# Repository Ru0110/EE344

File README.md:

# EE344
Auto-dialling Alarm System for Temperature and Humidity Monitoring

## File organization
The following folders will be present in the root directory of the project:
- `energy_meter`: Contains KiCad design files for the sensing unit PCB
- `Software`: Contains all firmware used in the project
    - `RP2040_code`: Source code for the firmware of the sensing unit written using the RP2040 C/C++ SDK. The code may be built using CMake or the uf2 file in the build subdirectory may be flashed directly to the RPi Pico W.
    - `arduino_code`: Source code for the sensing unit based on arduino. Based on code provided by Analog Devices for the EVAL-ACE9000 SHIELDZ board.
    - `central_code`: Source code for the central unit written in MicroPython
    - Other python files are for setting up a TCP client to test data logging
- `CAD`: Contains files for the enclosures of the sensing unit and central unit  
- `Test`: Contains test data from a long-term test using an Air Conditioner
- `central_unit`: Contains KiCad design files for a central unit with a SIM800L module. This is not used in the final prototype but may be useful for future iterations
- `Website`: Contains Code for a locally hosted website to view real-time data from the sensing units 
- Documentation file
- README file (this file)

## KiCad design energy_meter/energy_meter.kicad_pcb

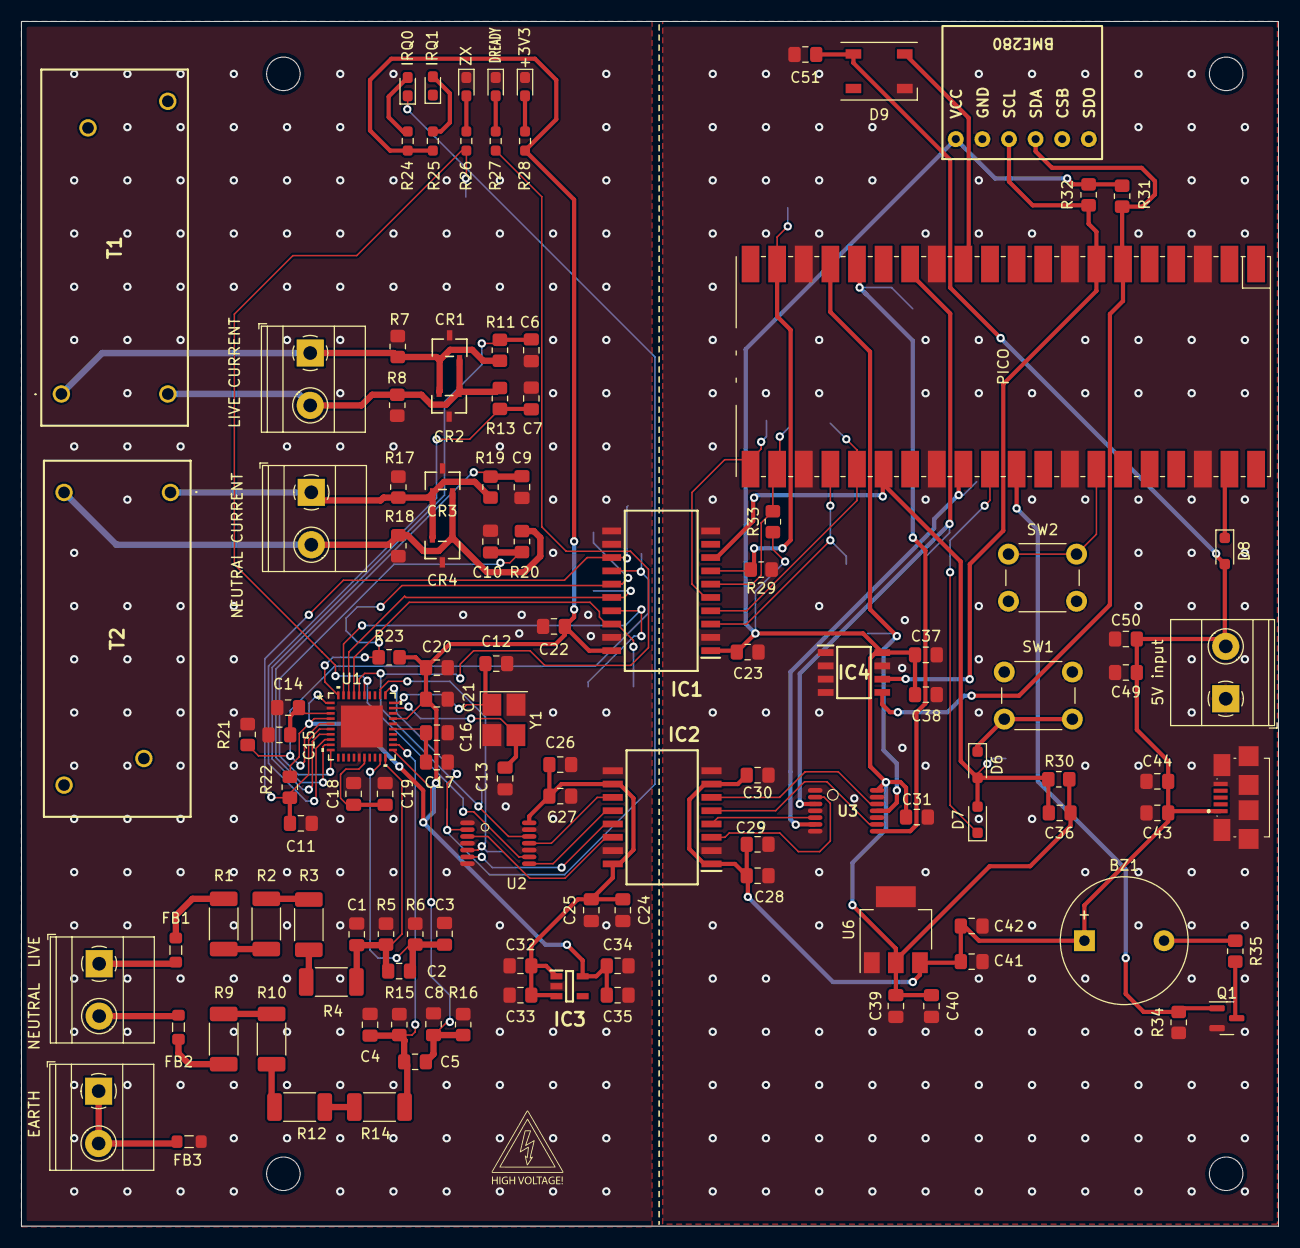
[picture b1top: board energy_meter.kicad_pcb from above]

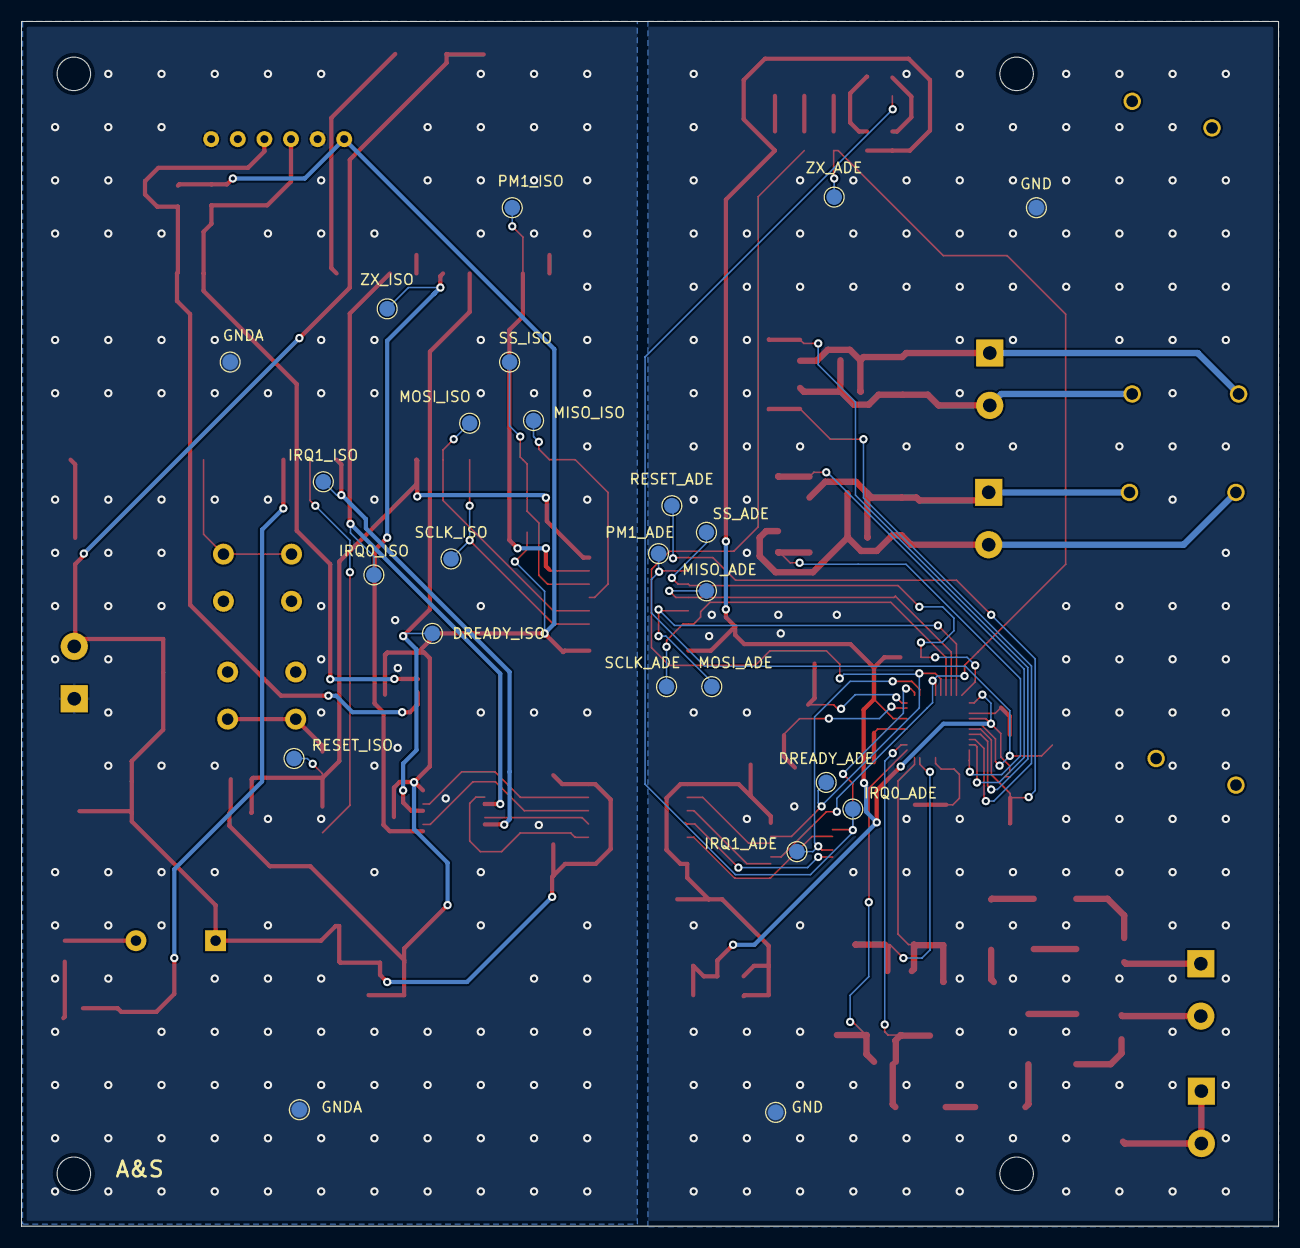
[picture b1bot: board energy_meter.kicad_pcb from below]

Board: 2 copper layers, 120.0 x 115.0 mm, 149 parts (24 on the bottom side), 77 nets.

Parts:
5V input: 5V_SMPS; TerminalBlock_Phoenix_MKDS-1,5-2_1x02_P5.00mm_Horizontal
+3V3: LED; LED_0603_1608Metric_Pad1.05x0.95mm_HandSolder
BZ1: Buzzer; Buzzer_12x9.5RM7.6
C1, C3, C4, C6, C7, C8, C9, C10: 0.022u; C_0805_2012Metric_Pad1.18x1.45mm_HandSolder
C2, C5: 51p; C_0805_2012Metric_Pad1.18x1.45mm_HandSolder
C11, C36: 1u; C_0805_2012Metric_Pad1.18x1.45mm_HandSolder
C12, C13: 18p; C_0805_2012Metric_Pad1.18x1.45mm_HandSolder
C14, C16, C18, C20, C22, C23, C24, C26, C28, C30, C31, C33, C35, C38, C39, C41, C44, C49, C51: 0.1u; C_0805_2012Metric_Pad1.18x1.45mm_HandSolder
C15, C17, C19, C37: 4.7u; C_0805_2012Metric_Pad1.18x1.45mm_HandSolder
C21, C25, C27, C29, C32, C34, C40, C42: 10u; C_0805_2012Metric_Pad1.18x1.45mm_HandSolder
C43, C50: 22u; C_0805_2012Metric_Pad1.18x1.45mm_HandSolder
CR1, CR2, CR3, CR4: MMBD4148SE; SOT-23TO-236_318-AT_OSI
D6, D7, D8: D_Schottky; D_SOD-323_HandSoldering
D9: WS2812B; LED_WS2812B_PLCC4_5.0x5.0mm_P3.2mm
DREADY: LED; LED_0603_1608Metric_Pad1.05x0.95mm_HandSolder
DREADY_ADE: TestPoint; TestPoint_Pad_D1.5mm
DREADY_ISO: TestPoint; TestPoint_Pad_D1.5mm
FB1, FB2, FB3: FerriteBead; L_0805_2012Metric_Pad1.05x1.20mm_HandSolder
GND: TestPoint; TestPoint_Pad_D1.5mm
GND#2: TestPoint; TestPoint_Pad_D1.5mm
GNDA: TestPoint; TestPoint_Pad_D1.5mm
GNDA#2: TestPoint; TestPoint_Pad_D1.5mm
H1, H2, H3, H4: MountingHole; MountingHole_3.2mm_M3
IC1: ADUM4151BRIZ; SOIC127P1031X264-20N
IC2: ADUM6404ARIZ; SOIC127P1032X265-16N
IC3: ADP122AUJZ-3.3-R7; SOT95P280X100-5N
IC4: 24LC32A_SN; SOIC127P600X175-8N
IRQ0, IRQ1: LED; LED_0603_1608Metric_Pad1.05x0.95mm_HandSolder
IRQ0_ADE, IRQ0_ISO, IRQ1_ADE, IRQ1_ISO: TestPoint; TestPoint_Pad_D1.5mm
J1, J2: Screw_Terminal_01x02; TerminalBlock_Phoenix_MKDS-1,5-2_1x02_P5.00mm_Horizontal
J3: MicroUSB; ZX62AB5PA31
LIVE CURRENT: IA_in; TerminalBlock_Phoenix_MKDS-1,5-2_1x02_P5.00mm_Horizontal
MISO_ADE: TestPoint; TestPoint_Pad_D1.5mm
MISO_ISO: TestPoint; TestPoint_Pad_D1.5mm
MOSI_ADE: TestPoint; TestPoint_Pad_D1.5mm
MOSI_ISO: TestPoint; TestPoint_Pad_D1.5mm
NEUTRAL CURRENT: IB_in; TerminalBlock_Phoenix_MKDS-1,5-2_1x02_P5.00mm_Horizontal
PICO: Pico_SMD_NODEBUG; RPi_PicoW_SMD
PM1_ADE, PM1_ISO: TestPoint; TestPoint_Pad_D1.5mm
Q1: Q_NMOS_SGD; SOT-23
R1, R2, R3, R4, R9, R10, R12, R14: 200k; R_2010_5025Metric_Pad1.40x2.65mm_HandSolder
R5, R6, R11, R13, R15, R16, R19, R20, R35: 1k; R_0805_2012Metric_Pad1.20x1.40mm_HandSolder
R7, R8, R17, R18: 40.2; R_0805_2012Metric_Pad1.20x1.40mm_HandSolder
R21: 10K; R_0805_2012Metric_Pad1.20x1.40mm_HandSolder
R22, R23, R29, R30, R31, R32, R33, R34: 10k; R_0805_2012Metric_Pad1.20x1.40mm_HandSolder
R24, R25, R26: 3K; R_0603_1608Metric_Pad0.98x0.95mm_HandSolder
R27, R28: 3k; R_0603_1608Metric_Pad0.98x0.95mm_HandSolder
RESET_ADE: TestPoint; TestPoint_Pad_D1.5mm
RESET_ISO: TestPoint; TestPoint_Pad_D1.5mm
SCLK_ADE: TestPoint; TestPoint_Pad_D1.5mm
SCLK_ISO: TestPoint; TestPoint_Pad_D1.5mm
SS_ADE: TestPoint; TestPoint_Pad_D1.5mm
SS_ISO: TestPoint; TestPoint_Pad_D1.5mm
SW1, SW2: SW_Push; SW_PUSH_6mm
T1: IA_in; T60404E4626X502
T2: IB_in; T60404E4626X502
U1: ADE9000ACPZ; ADE9000ACPZ_ADI
U2, U3: SN74LV4T125PWR; PW0014A_N
U5: BME280; BME_breakout
U6: AMS1117-3.3; SOT-223-3_TabPin2
Y1: Crystal_GND24; Crystal_SMD_3225-4Pin_3.2x2.5mm_HandSoldering
ZX: LED; LED_0603_1608Metric_Pad1.05x0.95mm_HandSolder
ZX_ADE: TestPoint; TestPoint_Pad_D1.5mm
ZX_ISO: TestPoint; TestPoint_Pad_D1.5mm

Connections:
+3V3_ADE: C20.1, C21.1, C22.1, C34.1, C35.1, IC1.20 (VDD2), IC3.5 (VOUT), R22.1, R23.2, R24.1, R25.1, R28.1, U1.1 (PULL_HIGH), U1.4 (PM0), U1.27 (VDD)
+3V3_ISO: C23.2, C31.1, C36.1, C37.1, C38.1, C39.1, C40.1, IC1.1 (VDD1), IC4.8 (VCC), R30.1, R31.1, R32.1, R33.1, U3.14 (VCC), U5.1 (VCC), U6.2 (VO)
+5V_ADE: C24.1, C25.1, C26.1, C27.1, C32.1, C33.1, IC2.10 (VSEL), IC2.16 (VISO), IC3.1 (VIN), IC3.3 (EN), U2.14 (VCC)
+5V_PICO: 5V input.2, BZ1.1 (+), C28.1, C29.1, C30.2, C41.1, C42.1, C43.1, C44.1, C49.1, C50.1, C51.1, D8.2 (A), D9.1 (VDD), IC2.1 (VDD1), IC2.7 (VDDL), J3.1, U6.3 (VI)
AVDDOUT: C16.1, C17.1, U1.25 (AVDDOUT)
BUZZER: PICO.31 (GPIO26_ADC0), Q1.1 (G), R34.1
DREADY_ADE: DREADY_ADE.1, R27.1, U1.36 (CF4/*EVENT/DREADY), U2.12 (4A)
DREADY_ISO: DREADY_ISO.1, PICO.17 (GPIO13), U3.11 (4Y)
DVDDOUT: C14.1, C15.1, U1.3 (DVDDOUT)
EARTH: FB3.2, J2.1, J2.2
GND: +3V3.1 (K), C1.2, C3.2, C4.2, C6.2, C7.1, C8.2, C9.2, C10.1, C11.2, C12.2, C13.2, C14.2, C15.2, C16.2, C17.2, C18.2, C19.2, C20.2, C21.2, C22.2, C24.2, C25.2, C26.2, C27.2, C32.2, C33.2, C34.2, C35.2, CR1.3, CR2.3, CR3.3, CR4.3, DREADY.1 (K), FB3.1, GND.1, GND#2.1, IC1.11 (GND2_1), IC1.12 (VIC), IC1.19 (GND2_2), IC2.9 (GNDISO_1), IC2.15 (GNDISO_2), IC3.2 (GND), R5.1, R6.1, R7.2, R8.1, R15.1, R16.1, R17.2, R18.1, R21.2, U1.2 (DGND), U1.15 (REFGND), U1.26 (AGND), U1.28 (GND), U1.41 (EPAD), U2.1 (1OE_N), U2.4 (2OE_N), U2.7 (GND), U2.10 (3OE_N), U2.13 (4OE_N), Y1.2, Y1.4, ZX.1 (K)
GNDA: 5V input.1, C23.1, C28.2, C29.2, C30.1, C31.2, C37.2, C38.2, C39.2, C40.2, C41.2, C42.2, C43.2, C44.2, C49.2, C50.2, C51.2, D9.3 (VSS), GNDA.1, GNDA#2.1, IC1.2 (GND1_1), IC1.10 (GND1_2), IC2.2 (GND1_1), IC2.8 (GND1_2), IC4.1 (A0), IC4.2 (A1), IC4.3 (A2), IC4.4 (VSS), IC4.7 (WP), J3.5, J3.MP1, J3.MP2, J3.MP3, J3.MP4, J3.MP5, J3.MP6, PICO.3 (GND), PICO.8 (GND), PICO.13 (GND), PICO.18 (GND), PICO.23 (GND), PICO.28 (GND), PICO.33 (AGND), PICO.38 (GND), Q1.2 (S), R29.1, R34.2, SW1.1, SW2.2, U3.1 (1OE_N), U3.4 (2OE_N), U3.7 (GND), U3.10 (3OE_N), U3.13 (4OE_N), U5.2 (GND), U5.6 (SDO), U6.1 (GND)
IAN: C7.2, R13.2, U1.8 (IAN)
IAP: C6.1, R11.2, U1.7 (IAP)
IBN: C10.2, R20.2, U1.10 (IBN)
IBP: C9.1, R19.2, U1.9 (IBP)
IRQ0_ADE: IRQ0.1 (K), IRQ0_ADE.1, U1.31 (*IRQ0), U2.2 (1A)
IRQ0_ISO: IRQ0_ISO.1, PICO.14 (GPIO10), U3.3 (1Y)
IRQ1_ADE: IRQ1_ADE.1, U1.32 (*IRQ1), U2.5 (2A)
IRQ1_ISO: IRQ1_ISO.1, PICO.29 (GPIO22), U3.6 (2Y)
MISO_ADE: IC1.16 (SO), MISO_ADE.1, U1.38 (MISO)
MISO_ISO: IC1.5 (MI), MISO_ISO.1, PICO.21 (GPIO16)
MOSI_ADE: IC1.17 (SI), MOSI_ADE.1, U1.39 (MOSI)
MOSI_ISO: IC1.4 (MO), MOSI_ISO.1, PICO.25 (GPIO19)
unnamed: BZ1.2 (-), R35.1
unnamed: IRQ0.2 (A), R24.2
unnamed: IRQ1.2 (A), R25.2
unnamed: R26.2, ZX.2 (A)
unnamed: DREADY.2 (A), R27.2
unnamed: +3V3.2 (A), R28.2
unnamed: D6.1 (K), SW1.2
unnamed: D8.1 (K), PICO.39 (VSYS)
unnamed: FB1.1, R1.1
unnamed: FB2.1, R9.1
unnamed: IC2.14 (VIA), U2.3 (1Y)
unnamed: IC2.13 (VIB), U2.6 (2Y)
unnamed: IC2.12 (VIC), U2.8 (3Y)
unnamed: IC2.11 (VID), U2.11 (4Y)
unnamed: IC2.3 (VOA), U3.2 (1A)
unnamed: IC2.4 (VOB), U3.5 (2A)
unnamed: IC2.5 (VOC), U3.9 (3A)
unnamed: IC2.6 (VOD), U3.12 (4A)
unnamed: CR1.1, CR2.2, LIVE CURRENT.1, R7.1, R11.1, T1.1
unnamed: CR1.2, CR2.1, LIVE CURRENT.2, R8.2, R13.1, T1.4
unnamed: CR3.1, CR4.2, NEUTRAL CURRENT.1, R17.1, R19.1, T2.1
unnamed: CR3.2, CR4.1, NEUTRAL CURRENT.2, R18.2, R20.1, T2.4
unnamed: Q1.3 (D), R35.2
unnamed: R1.2, R2.1
unnamed: R2.2, R3.1
unnamed: R3.2, R4.1
unnamed: R9.2, R10.1
unnamed: R10.2, R12.1
unnamed: R12.2, R14.1
unnamed: C13.1, U1.29 (CLKIN), Y1.3
unnamed: C12.1, U1.30 (CLKOUT), Y1.1
unnamed: PICO.34 (GPIO28_ADC2), SW2.1
PM1_ADE: IC1.14 (VOA), PM1_ADE.1, R21.1, U1.5 (PM1)
PM1_ISO: IC1.7 (VIA), PICO.19 (GPIO14), PM1_ISO.1, R29.2
REF: C18.1, C19.1, U1.16 (REF)
RESET_ADE: C11.1, IC1.13 (VOB), R22.2, RESET_ADE.1, U1.6 (*RESET)
RESET_ISO: C36.2, D6.2 (A), D7.2 (A), IC1.8 (VIB), PICO.26 (GPIO20), R30.2, RESET_ISO.1
RESET_PICO: D7.1 (K), PICO.30 (RUN)
SCLK_ADE: IC1.18 (SCLK), SCLK_ADE.1, U1.37 (SCLK)
SCLK_ISO: IC1.3 (MCLK), PICO.24 (GPIO18), SCLK_ISO.1
SCL_PICO: IC4.6 (SCL), PICO.7 (GPIO5), R32.2, U5.3 (SCL)
SDA_PICO: IC4.5 (SDA), PICO.6 (GPIO4), R31.2, U5.4 (SDA)
SS_ADE: IC1.15 (~SSS), R23.1, SS_ADE.1, U1.40 (*SS)
SS_ISO: IC1.6 (~MSS), PICO.22 (GPIO17), R33.2, SS_ISO.1
VA: FB1.2, J1.1
VAN: C2.2, C3.1, R6.2, U1.19 (VAN)
VAP: C1.1, C2.1, R4.2, R5.2, U1.20 (VAP)
VB: FB2.2, J1.2
VBN: C5.2, C8.1, R16.2, U1.21 (VBN)
VBP: C4.1, C5.1, R14.2, R15.2, U1.22 (VBP)
WS_LED: D9.4 (DIN), PICO.12 (GPIO9)
ZX_ADE: R26.1, U1.35 (CF3/ZX), U2.9 (3A), ZX_ADE.1
ZX_ISO: PICO.16 (GPIO12), U3.8 (3Y), ZX_ISO.1

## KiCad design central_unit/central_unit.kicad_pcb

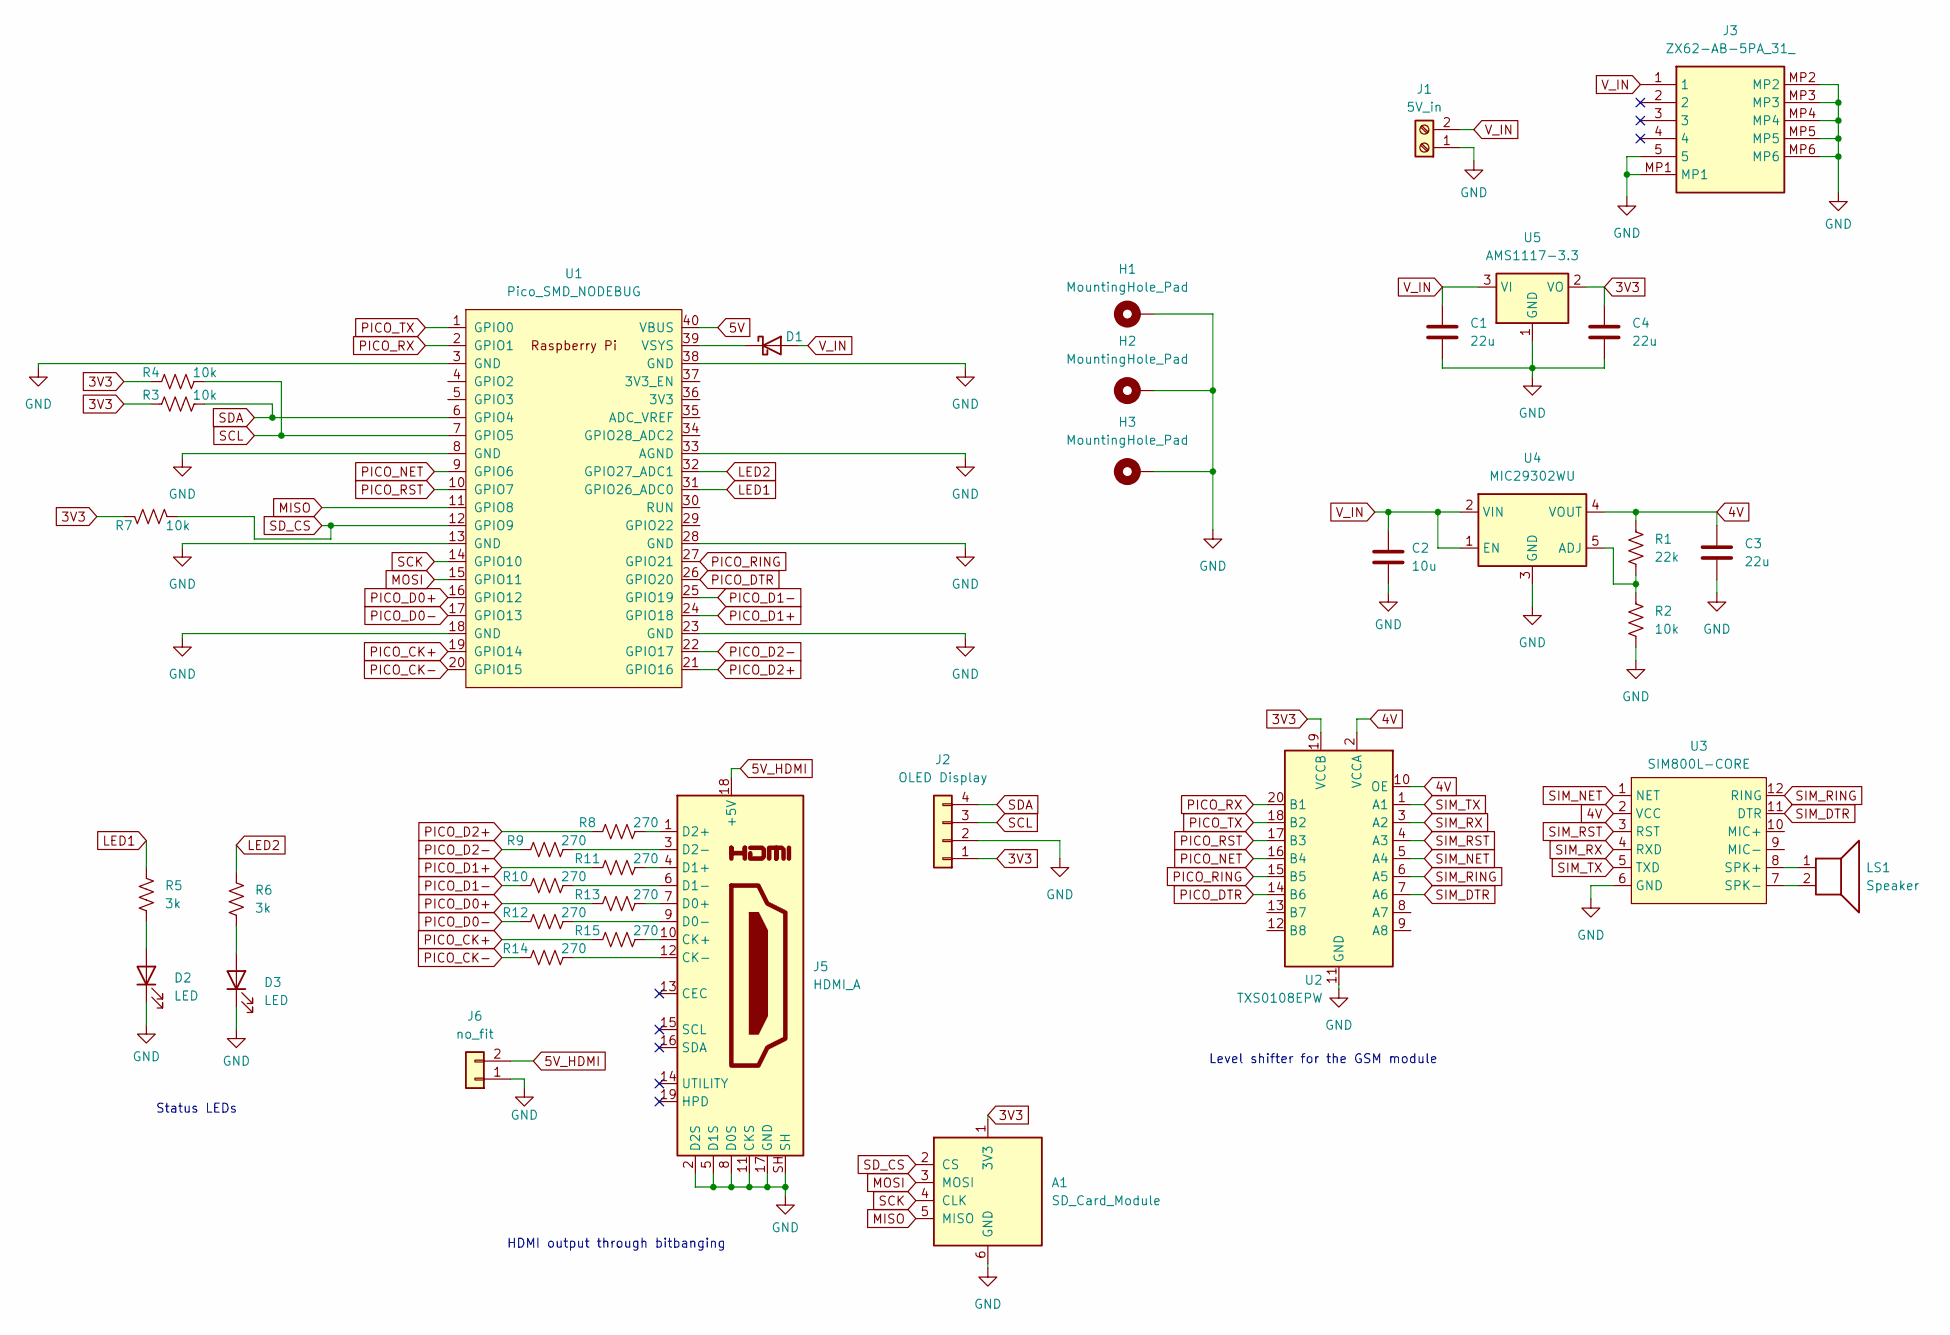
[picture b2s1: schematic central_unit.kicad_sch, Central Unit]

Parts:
A1: SD_Card_Module
C1, C3, C4: 22u; C_0805_2012Metric_Pad1.18x1.45mm_HandSolder
C2: 10u; C_0805_2012Metric_Pad1.18x1.45mm_HandSolder
D1: D_Schottky; D_SOD-323_HandSoldering
D2, D3: LED; LED_0603_1608Metric_Pad1.05x0.95mm_HandSolder
H1, H2, H3: MountingHole_Pad; MountingHole_3.2mm_M3_Pad_Via
J1: 5V_in; TerminalBlock_Phoenix_MKDS-1,5-2_1x02_P5.00mm_Horizontal
J2: OLED Display; 128x64OLED
J3: ZX62-AB-5PA_31_; ZX62AB5PA31; Mouser Part Number 798-ZX62-AB-5PA31
J5: HDMI_A; HDMI_A_Molex_208658-1001_Horizontal
J6: no_fit; PinHeader_1x02_P2.54mm_Vertical
LS1: Speaker; Buzzer_12x9.5RM7.6
R1: 22k; R_0805_2012Metric_Pad1.20x1.40mm_HandSolder
R2, R3, R4, R7: 10k; R_0805_2012Metric_Pad1.20x1.40mm_HandSolder
R5, R6: 3k; R_0805_2012Metric_Pad1.20x1.40mm_HandSolder
R8, R9, R10, R11, R12, R13, R14, R15: 270; R_0805_2012Metric_Pad1.20x1.40mm_HandSolder
U1: Pico_SMD_NODEBUG; RPi_Pico_SMD
U2: TXS0108EPW; TSSOP-20_4.4x6.5mm_P0.65mm
U3: SIM800L-CORE
U4: MIC29302WU; TO-263-5_TabPin3
U5: AMS1117-3.3; SOT-223-3_TabPin2

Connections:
3V3: A1.1 (3V3), C4.1, J2.1, R3.1, R4.1, R7.1, U2.19 (VCCB), U5.2 (VO)
4V: C3.1, R1.2, U2.2 (VCCA), U2.10 (OE), U3.2 (VCC), U4.4 (VOUT)
5V: U1.40 (VBUS)
5V_HDMI: J5.18 (+5V), J6.2
GND: A1.6 (GND), C1.2, C2.2, C3.2, C4.2, D2.1 (K), D3.1 (K), H1.1, H2.1, H3.1, J1.1, J2.2, J3.5, J3.MP1, J3.MP2, J3.MP3, J3.MP4, J3.MP5, J3.MP6, J5.2 (D2S), J5.5 (D1S), J5.8 (D0S), J5.11 (CKS), J5.17 (GND), J5.SH, J6.1, R2.1, U1.3 (GND), U1.8 (GND), U1.13 (GND), U1.18 (GND), U1.23 (GND), U1.28 (GND), U1.33 (AGND), U1.38 (GND), U2.11 (GND), U3.6 (GND), U4.3 (GND), U5.1 (GND)
LED1: R5.1, U1.31 (GPIO26_ADC0)
LED2: R6.1, U1.32 (GPIO27_ADC1)
MISO: A1.5 (MISO), U1.11 (GPIO8)
MOSI: A1.3 (MOSI), U1.15 (GPIO11)
unnamed: D1.1 (K), U1.39 (VSYS)
unnamed: D2.2 (A), R5.2
unnamed: D3.2 (A), R6.2
unnamed: J5.10 (CK+), R15.2
unnamed: J5.12 (CK-), R14.2
unnamed: J5.7 (D0+), R13.2
unnamed: J5.9 (D0-), R12.2
unnamed: J5.4 (D1+), R11.2
unnamed: J5.6 (D1-), R10.2
unnamed: J5.1 (D2+), R8.2
unnamed: J5.3 (D2-), R9.2
unnamed: LS1.1, U3.8 (SPK+)
unnamed: LS1.2, U3.7 (SPK-)
unnamed: R1.1, R2.2, U4.5 (ADJ)
PICO_CK+: R15.1, U1.19 (GPIO14)
PICO_CK-: R14.1, U1.20 (GPIO15)
PICO_D0+: R13.1, U1.16 (GPIO12)
PICO_D0-: R12.1, U1.17 (GPIO13)
PICO_D1+: R11.1, U1.24 (GPIO18)
PICO_D1-: R10.1, U1.25 (GPIO19)
PICO_D2+: R8.1, U1.21 (GPIO16)
PICO_D2-: R9.1, U1.22 (GPIO17)
PICO_DTR: U1.26 (GPIO20), U2.14 (B6)
PICO_NET: U1.9 (GPIO6), U2.16 (B4)
PICO_RING: U1.27 (GPIO21), U2.15 (B5)
PICO_RST: U1.10 (GPIO7), U2.17 (B3)
PICO_RX: U1.2 (GPIO1), U2.20 (B1)
PICO_TX: U1.1 (GPIO0), U2.18 (B2)
SCK: A1.4 (CLK), U1.14 (GPIO10)
SCL: J2.3, R4.2, U1.7 (GPIO5)
SDA: J2.4, R3.2, U1.6 (GPIO4)
SD_CS: A1.2 (CS), R7.2, U1.12 (GPIO9)
SIM_DTR: U2.7 (A6), U3.11 (DTR)
SIM_NET: U2.5 (A4), U3.1 (NET)
SIM_RING: U2.6 (A5), U3.12 (RING)
SIM_RST: U2.4 (A3), U3.3 (RST)
SIM_RX: U2.3 (A2), U3.4 (RXD)
SIM_TX: U2.1 (A1), U3.5 (TXD)
V_IN: C1.1, C2.1, D1.2 (A), J1.2, J3.1, U4.1 (EN), U4.2 (VIN), U5.3 (VI)

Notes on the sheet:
Level shifter for the GSM module
Status LEDs
HDMI output through bitbanging

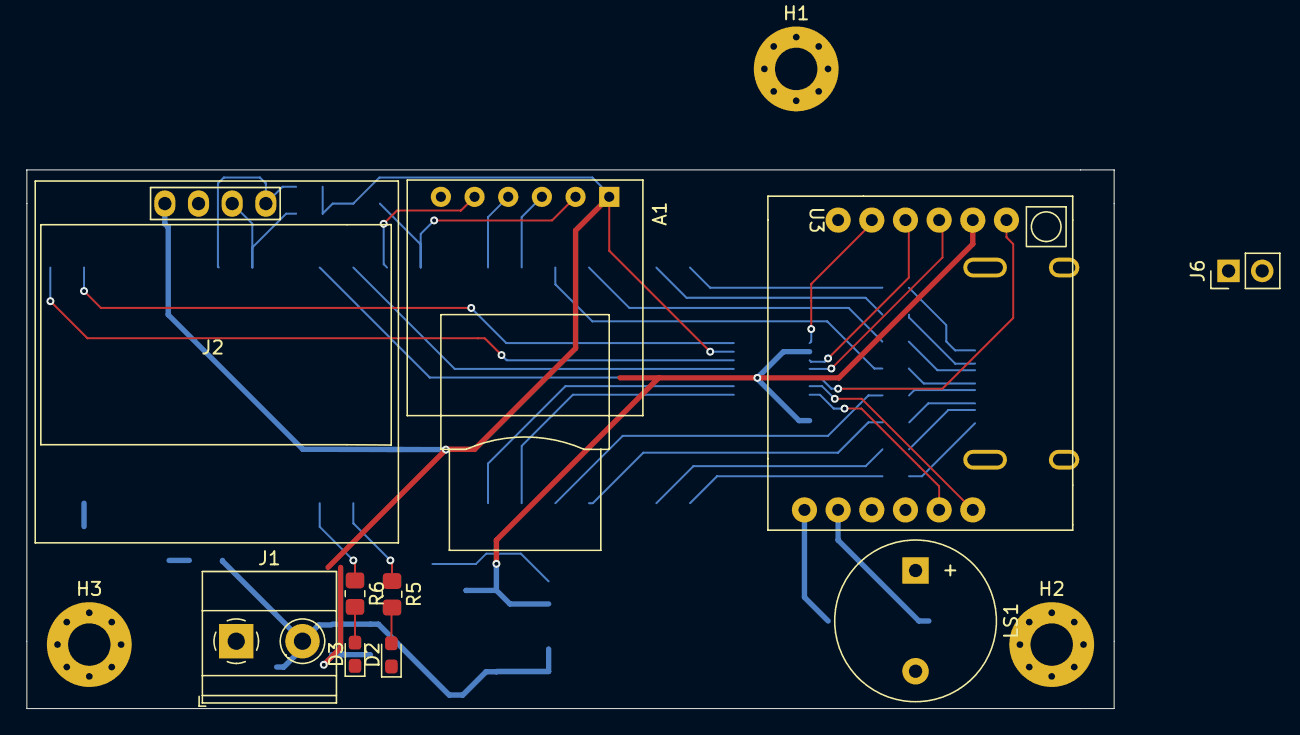
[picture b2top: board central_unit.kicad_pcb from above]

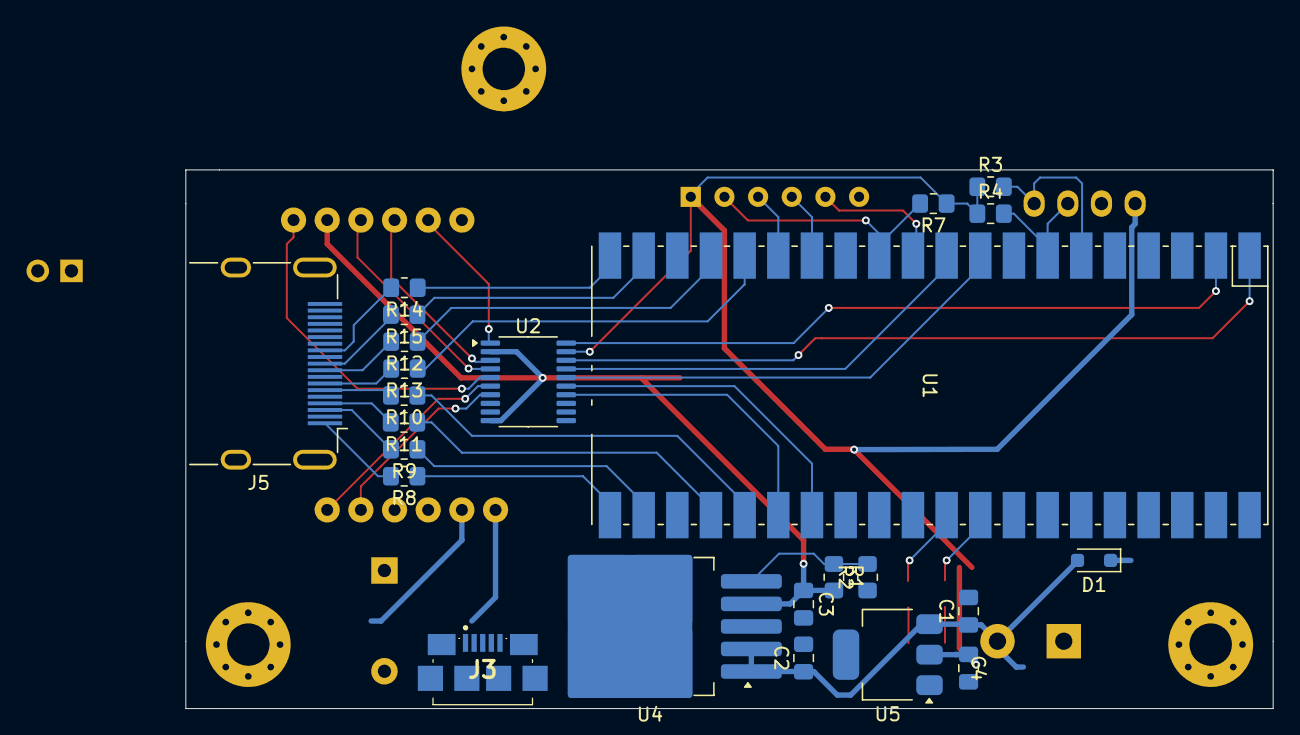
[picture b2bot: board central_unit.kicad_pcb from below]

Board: 2 copper layers, 82.0 x 40.6 mm, 37 parts (24 on the bottom side), 47 nets.

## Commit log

2024-02-13 Add init schematic
2024-02-20 Schematic progress
2024-03-03 Progress in schematic
2024-03-03 Remove icon
2024-03-03 Finish up schematic
2024-03-03 Add lipo battery terminal
2024-03-03 Minor changes
2024-03-04 finish schematic started on layout
2024-03-05 Add pdf of schematic
2024-03-10 Example code
2024-03-12 Synchronize
2024-03-12 Add central unit
2024-03-12 Initial ade9000 driver
2024-03-13 Change definitions of pins
2024-03-13 rearrange
2024-03-16 Remove banana cliffs
2024-03-16 Basic layout
2024-03-16 Again
2024-03-16 finished layout
2024-03-16 Restore libraries
2024-03-16 more libraries
2024-03-17 pcb routing1
2024-03-17 Complete routing of sensing unit
2024-03-19 Silkscreen done
2024-03-20 Add bitmaps
2024-03-27 Major progress
2024-03-28 Conversion factors added to Arduino code
2024-03-29 C API works!
2024-03-30 Finish interface with bme280
2024-04-01 oh bhai tcp
2024-04-03 Get upto date
2024-04-04 Catch up
2024-04-12 Prototype ready!
2024-04-15 Prepare for final submission
2024-04-16 Rename sample_code.py to waveform_plot.py
2024-04-16 Rename Waveform_plot.png to Waveform_plot2.png
2024-04-19 docs
